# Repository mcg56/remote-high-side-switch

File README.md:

# remote-high-side-switch
Connect to WiFI and enter IP address 192.168.4.1

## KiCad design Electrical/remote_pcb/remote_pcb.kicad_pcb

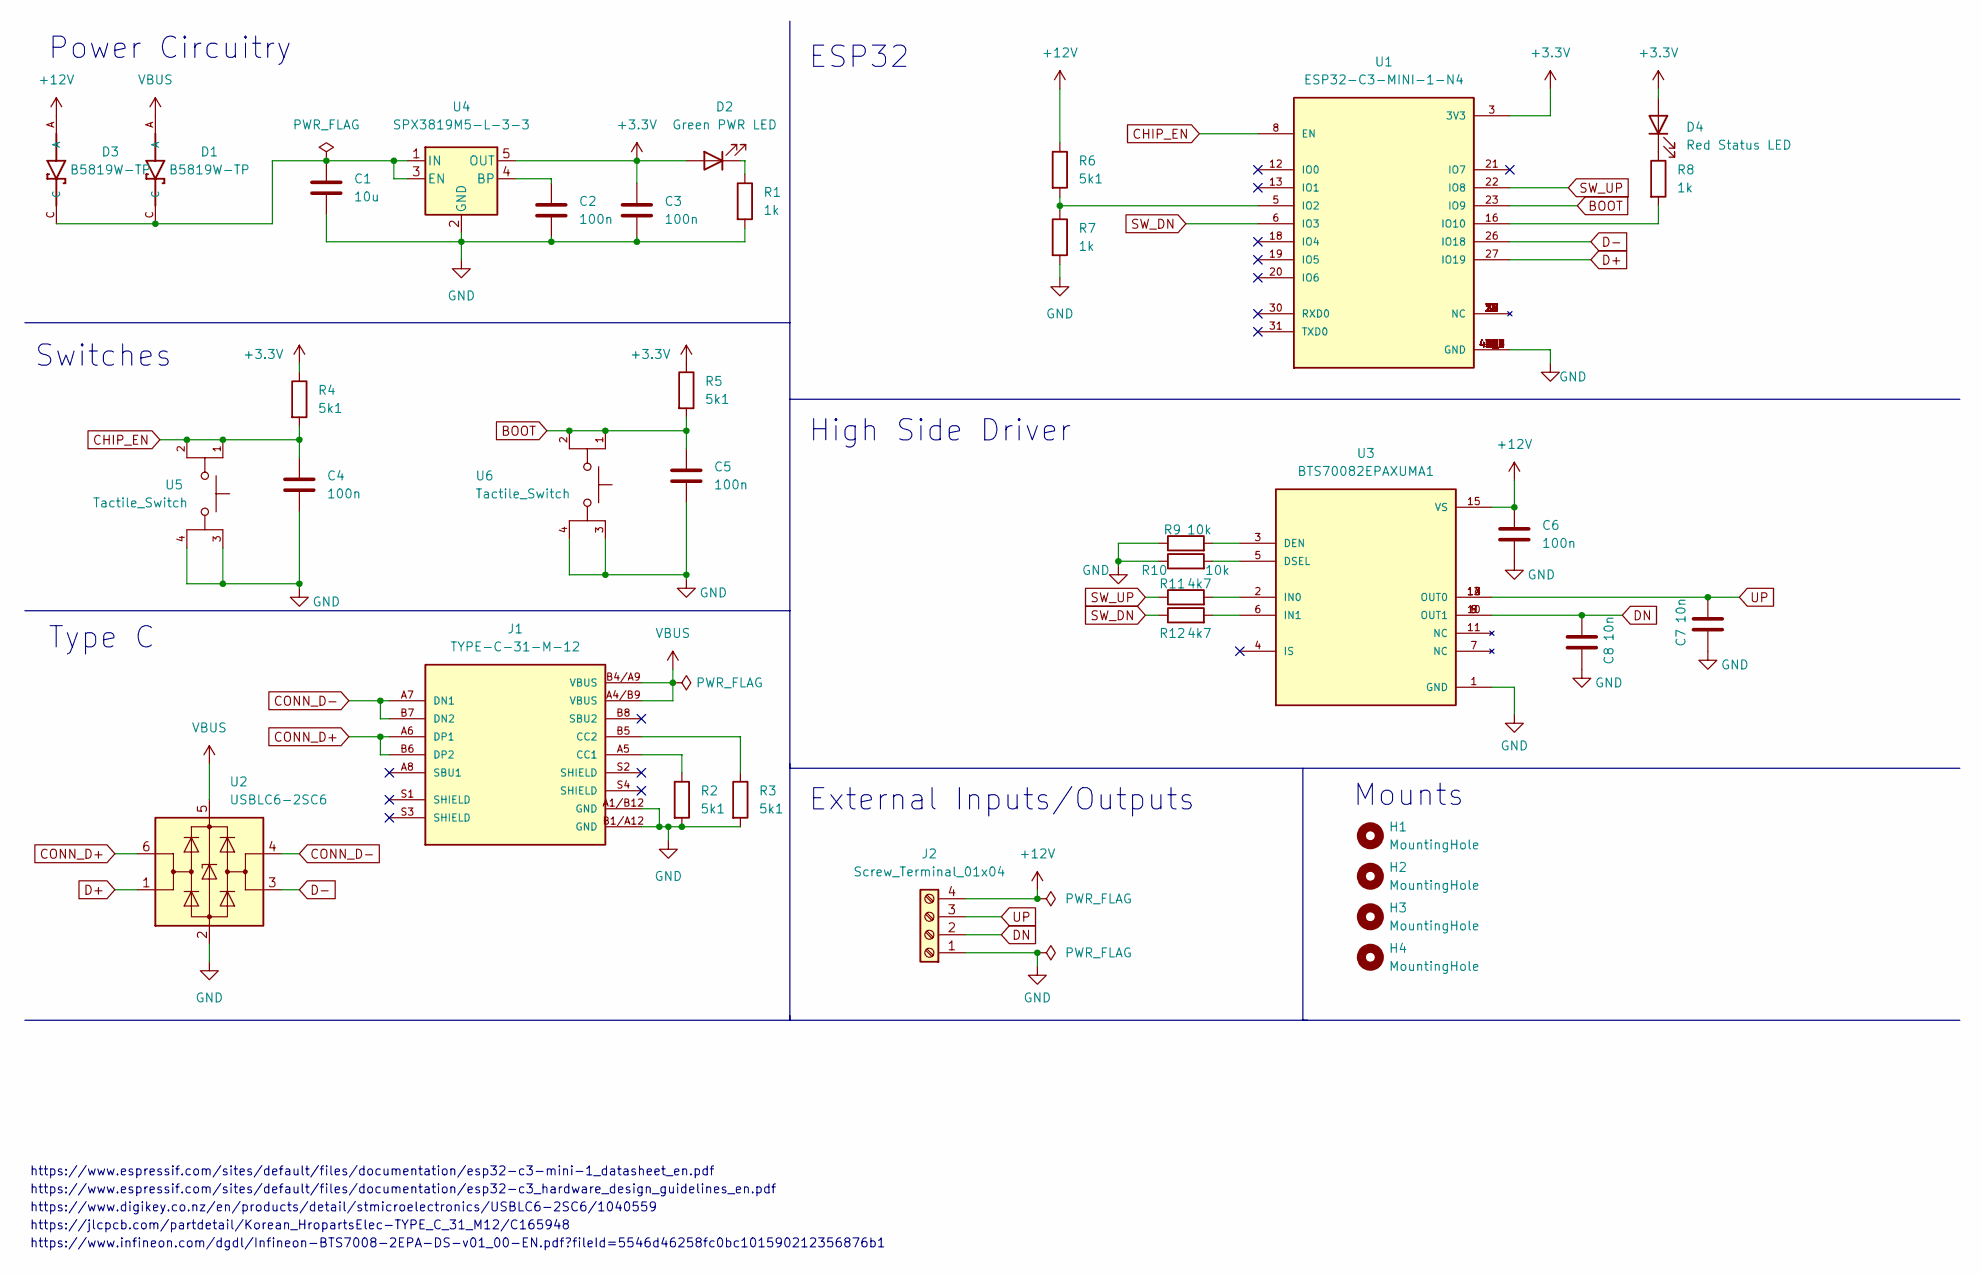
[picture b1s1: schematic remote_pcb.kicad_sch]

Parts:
C1: 10u; C_0603_1608Metric
C2, C3, C4, C5, C6: 100n; C_0603_1608Metric
C7, C8: 10n; C_0603_1608Metric
D1, D3: B5819W-TP; SOD3716X135N
D2: Green PWR LED; LED_0603_1608Metric
D4: Red Status LED; LED_0603_1608Metric
H1, H2, H3, H4: MountingHole; MountingHole_3.2mm_M3
J1: TYPE-C-31-M-12; PARTREV 2020.12.08
J2: Screw_Terminal_01x04; TerminalBlock_Phoenix_PT-1,5-4-3.5-H_1x04_P3.50mm_Horizontal
R1, R7, R8: 1k; R_0603_1608Metric
R2, R3, R4, R5, R6: 5k1; R_0603_1608Metric
R9, R10: 10k; R_0603_1608Metric
R11, R12: 4k7; R_0603_1608Metric
U1: ESP32-C3-MINI-1-N4; XCVR_ESP32-C3-MINI-1-N4; PARTREV v1.0
U2: USBLC6-2SC6; SOT-23-6
U3: BTS70082EPAXUMA1; SOP65P600X115-15N; PARTREV 1.14
U4: SPX3819M5-L-3-3; SOT-23-5
U5, U6: Tactile_Switch; Tactile Switch

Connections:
+3.3V: C3.1, D2.2 (A), D4.2 (A), R4.1, R5.1, U1.3 (3V3), U4.5 (OUT)
+12V: C6.1, D3.A, J2.4, R6.1, U3.15 (VS)
BOOT: C5.1, R5.2, U1.23 (IO9), U6.1, U6.2
CHIP_EN: C4.1, R4.2, U1.8 (EN), U5.1, U5.2
CONN_D+: J1.A6 (DP1), J1.B6 (DP2), U2.6 (I/O1)
CONN_D-: J1.A7 (DN1), J1.B7 (DN2), U2.4 (I/O2)
D+: U1.27 (IO19), U2.1 (I/O1)
D-: U1.26 (IO18), U2.3 (I/O2)
DN: C8.1, J2.2, U3.8 (OUT1), U3.9 (OUT1), U3.10 (OUT1)
GND: C1.2, C2.2, C3.2, C4.2, C5.2, C6.2, C7.1, C8.2, J1.A1/B12 (GND), J1.B1/A12 (GND), J2.1, R1.2, R2.2, R3.2, R7.2, R9.1, R10.1, U1.1 (GND), U1.2 (GND), U1.11 (GND), U1.14 (GND), U1.36 (GND), U1.37 (GND), U1.38 (GND), U1.39 (GND), U1.40 (GND), U1.41 (GND), U1.42 (GND), U1.43 (GND), U1.44 (GND), U1.45 (GND), U1.46 (GND), U1.47 (GND), U1.48 (GND), U1.49_1 (GND), U1.49_2 (GND), U1.49_3 (GND), U1.49_4 (GND), U1.49_5 (GND), U1.49_6 (GND), U1.49_7 (GND), U1.49_8 (GND), U1.49_9 (GND), U1.50 (GND), U1.51 (GND), U1.52 (GND), U1.53 (GND), U2.2 (GND), U3.1 (GND), U4.2 (GND), U5.3, U5.4, U6.3, U6.4
unnamed: C1.1, D1.C, D3.C, U4.1 (IN), U4.3 (EN)
unnamed: C2.1, U4.4 (BP)
unnamed: D2.1 (K), R1.1
unnamed: D4.1 (K), R8.1
unnamed: J1.A5 (CC1), R2.1
unnamed: J1.B5 (CC2), R3.1
unnamed: R6.2, R7.1, U1.5 (IO2)
unnamed: R8.2, U1.16 (IO10)
unnamed: R9.2, U3.3 (DEN)
unnamed: R10.2, U3.5 (DSEL)
unnamed: R11.2, U3.2 (IN0)
unnamed: R12.2, U3.6 (IN1)
SW_DN: R12.1, U1.6 (IO3)
SW_UP: R11.1, U1.22 (IO8)
UP: C7.2, J2.3, U3.12 (OUT0), U3.13 (OUT0), U3.14 (OUT0)
VBUS: D1.A, J1.A4/B9 (VBUS), J1.B4/A9 (VBUS), U2.5 (VBUS)

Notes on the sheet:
Switches
https://www.espressif.com/sites/default/files/documentation/esp32-c3_hardware_design_guidelines_en.pdf
External Inputs/Outputs
https://jlcpcb.com/partdetail/Korean_HropartsElec-TYPE_C_31_M12/C165948
High Side Driver
ESP32
https://www.espressif.com/sites/default/files/documentation/esp32-c3-mini-1_datasheet_en.pdf
Mounts
Type C
https://www.infineon.com/dgdl/Infineon-BTS7008-2EPA-DS-v01_00-EN.pdf?fileId=5546d46258fc0bc101590212356876b1
https://www.digikey.co.nz/en/products/detail/stmicroelectronics/USBLC6-2SC6/1040559
Power Circuitry

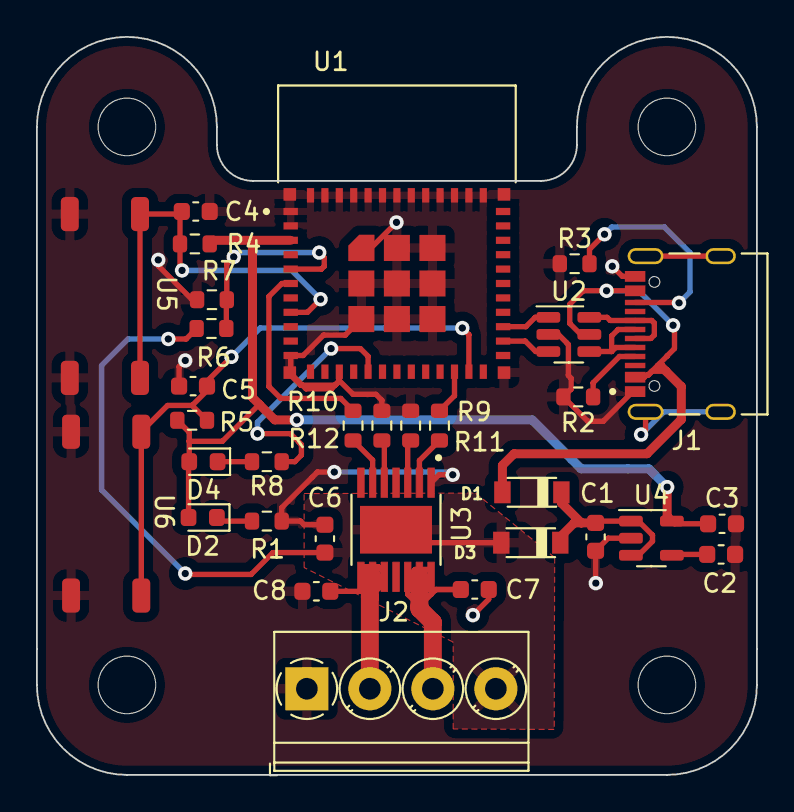
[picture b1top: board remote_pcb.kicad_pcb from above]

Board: 2 copper layers, 40.0 x 41.0 mm, 36 parts (0 on the bottom side), 26 nets.

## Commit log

2023-05-22 Adding existing files
